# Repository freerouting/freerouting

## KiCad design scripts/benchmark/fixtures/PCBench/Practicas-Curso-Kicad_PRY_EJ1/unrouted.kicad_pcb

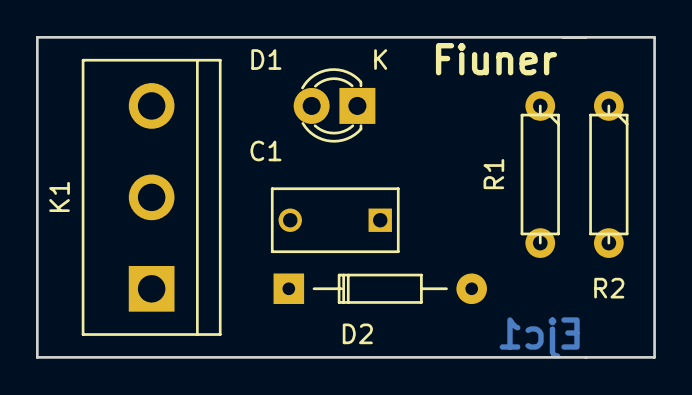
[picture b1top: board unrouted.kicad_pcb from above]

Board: 2 copper layers, 34.3 x 17.8 mm, 6 parts (0 on the bottom side), 4 nets, no tracks yet.

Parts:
C1: C; C_Rect_L7_W3.5_P5
D1: LED; LED-3MM
D2: D; Diode_DO-35_SOD27_Horizontal_RM10
K1: CONN_3; bornier3
R1: 100K; R3-LARGE_PADS
R2: 200K; R3-LARGE_PADS

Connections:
unnamed: C1.1, D1.1, R1.1, R2.1
unnamed: C1.2, D1.2, K1.3
unnamed: D2.1, K1.1
unnamed: D2.2, R1.2, R2.2

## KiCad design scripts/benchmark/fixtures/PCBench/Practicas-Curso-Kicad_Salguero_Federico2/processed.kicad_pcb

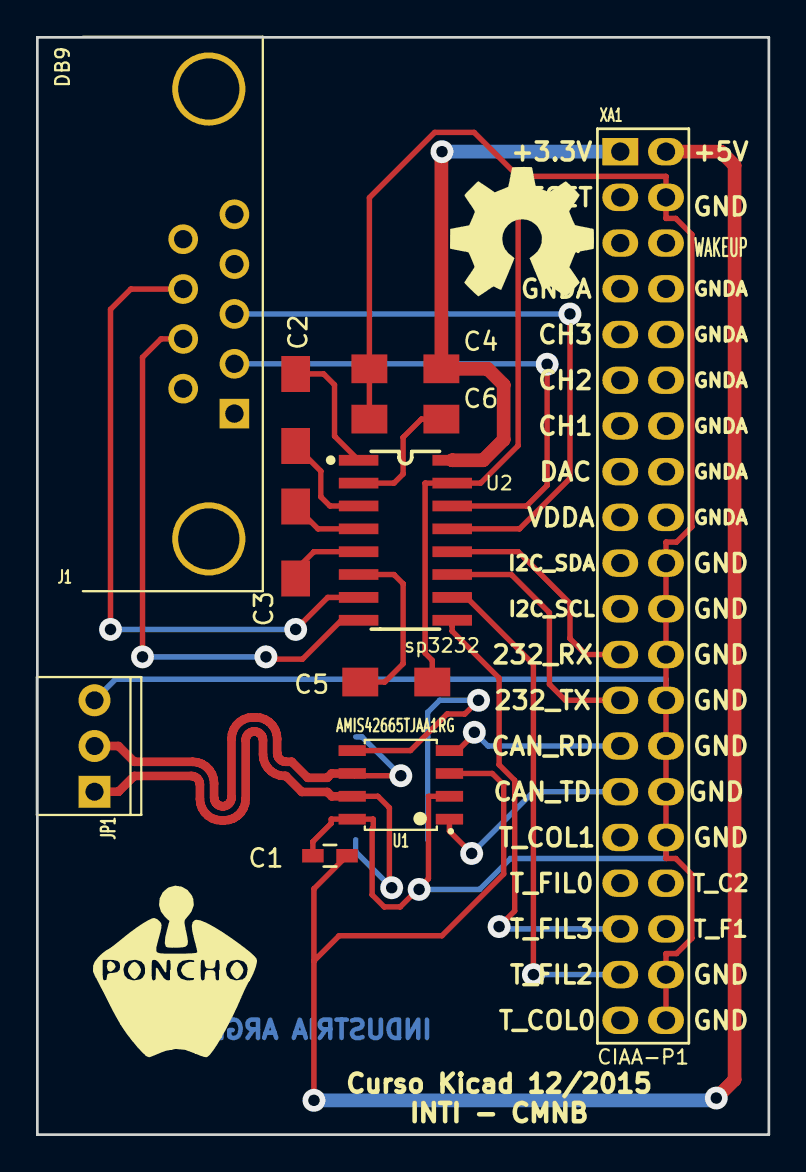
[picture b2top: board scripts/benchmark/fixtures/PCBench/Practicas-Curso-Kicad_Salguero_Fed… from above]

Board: 2 copper layers, 40.6 x 61.0 mm, 15 parts (0 on the bottom side), 22 nets.

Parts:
C1: C; C_0603_HandSoldering
C2, C3, C4, C5, C6: C; C_1206_HandSoldering
G101: Logo_OSHWA
Gxxx: LOGO; Logo_Poncho
J1: DB9; DB9_F_TH
JP1: CONN_3; CON_PALETA_3
R1, R2: R; R_1206_HandSoldering
U1: AMIS42665TJAA1RG; SOIC-8
U2: sp3232; SP3232ECN-SOIC16N
XA1: Conn_Poncho2P_2x_20x2; Conn_Poncho_Derecha

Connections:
+3.3V: C6.1, U2.16, XA1.1
+5V: C1.2, U1.3, XA1.2
/conector/CAN_N: JP1.2, R2.2, U1.6
/conector/CAN_P: JP1.1, R1.1, U1.7
/conector/CAN_RX: U1.4, XA1.27
/conector/CAN_TX: U1.1, XA1.29
/conector/CTS: U2.10, XA1.37
/conector/RTS: U2.9, XA1.35
/conector/RXD: U2.11, XA1.25
/conector/TXD: U2.12, XA1.23
GND: C1.1, C4.1, C5.1, C6.2, JP1.3, U1.2, U1.8, U2.15, XA1.4, XA1.20, XA1.22, XA1.24, XA1.26, XA1.28, XA1.30, XA1.32, XA1.38, XA1.40
unnamed: C2.1, U2.1
unnamed: C2.2, U2.3
unnamed: C3.1, U2.4
unnamed: C3.2, U2.5
unnamed: C4.2, U2.2
unnamed: C5.2, U2.6
unnamed: J1.2, U2.14
unnamed: J1.3, U2.13
unnamed: J1.7, U2.8
unnamed: J1.8, U2.7
unnamed: R1.2, R2.1, U1.5

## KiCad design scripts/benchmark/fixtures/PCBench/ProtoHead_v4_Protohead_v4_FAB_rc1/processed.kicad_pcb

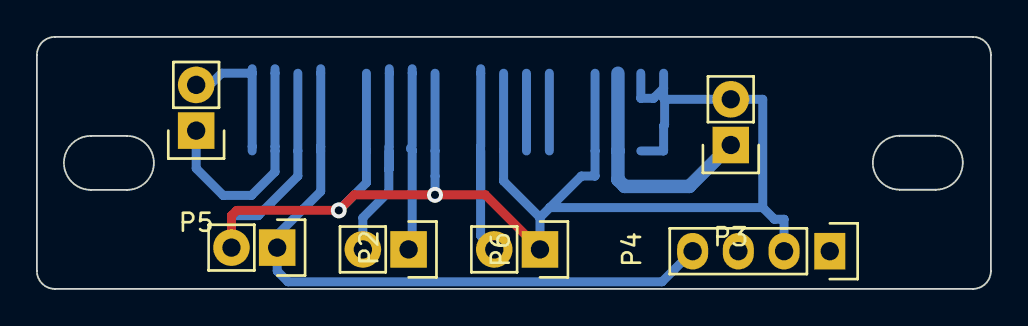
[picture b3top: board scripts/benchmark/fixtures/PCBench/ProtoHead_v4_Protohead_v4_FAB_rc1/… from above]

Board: 2 copper layers, 53.0 x 14.0 mm, 7 parts (1 on the bottom side), 8 nets.

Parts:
P1: FABTOTUM_HEAD_NOMOTOR_CONNECTOR; IntegratedBourns_nomotor_smd
P2: FAN; Pin_Header_Straight_1x02
P3: HEATER; Pin_Header_Straight_1x02
P4: BLOWER; Pin_Header_Straight_1x02
P5: THERMISTOR; Pin_Header_Straight_1x02
P6: I2C; Pin_Header_Straight_1x02
P7: Arduino_Mini_RAW_GND_RST_VCC; Socket_Strip_Straight_1x04

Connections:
GND: P1.1, P1.2, P1.4, P1.7, P1.9, P1.12, P1.14, P2.2, P3.2, P4.1, P7.2
unnamed: P1.3, P3.1
unnamed: P1.8, P4.2
unnamed: P1.10, P6.1
unnamed: P1.11, P6.2
unnamed: P1.13, P2.1, P7.4
unnamed: P1.15, P5.1
unnamed: P1.16, P5.2
